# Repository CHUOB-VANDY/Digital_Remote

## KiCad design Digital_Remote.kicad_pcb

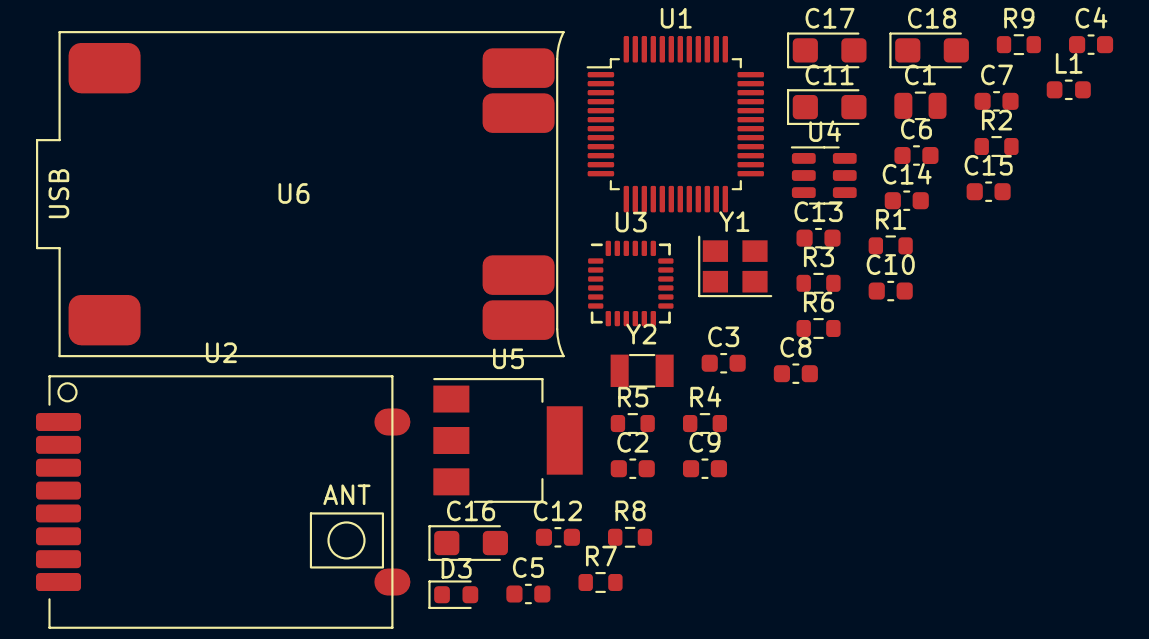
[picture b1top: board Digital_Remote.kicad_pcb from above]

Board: 2 copper layers, 37 parts (0 on the bottom side), 24 nets, no tracks yet.

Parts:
C1: 4.7u; C_0805_2012Metric
C2, C3, C4, C5, C13, C14: 100n; C_0603_1608Metric
C6: 1u; C_0603_1608Metric
C7, C8, C9, C10: 20p; C_0603_1608Metric
C11, C16, C17, C18: 22uF/6V; CP_EIA-3216-10_Kemet-I
C12: 10n; C_0603_1608Metric
C15: 2.2n; C_0603_1608Metric
D3: LED_Small; LED_0603_1608Metric
L1: 4.7nH; L_0603_1608Metric
R1, R2, R6: 10k; R_0603_1608Metric
R3, R4, R5: 4k7; R_0603_1608Metric
R7: 24k; R_0603_1608Metric
R8: 3k3; R_0603_1608Metric
R9: 1k; R_0603_1608Metric
U1: STM32F103C8Tx; LQFP-48_7x7mm_P0.5mm
U2: AS01-SPI
U3: MPU-6050; InvenSense_QFN-24_4x4mm_P0.5mm
U4: MT3608; SOT-23-6
U5: AMS1117-3.3; SOT-223-3_TabPin2
U6: TP4056
Y1: 8Mhz; Crystal_SMD_3225-4Pin_3.2x2.5mm
Y2: 32KHz; Crystal_SMD_3215-2Pin_3.2x1.5mm

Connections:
+3.3VA: C5.1, C6.1, L1.2, U1.9 (VDDA)
+3V3: C1.1, C2.1, C3.1, C4.1, C11.1, C12.2, C13.1, C18.1, L1.1, R1.1, R3.1, R4.1, R9.1, U1.24 (VDD), U1.36 (VDD), U1.48 (VDD), U2.1 (VCC), U3.8 (VDDIO), U3.13 (VDD), U5.2 (VO)
+5V: C17.1, R7.1, U5.3 (VI)
/BOOTO: R2.2, U1.44 (BOOT0)
/Buzzer: R5.1, U1.38 (PA15)
/CPOUT: C15.1, U3.20 (CPOUT)
/HSE_IN: C7.1, U1.5 (PD0), Y1.1
/HSE_OUT: C8.1, U1.6 (PD1), Y1.3
/I2C1_SCL: R3.2, U1.21 (PB10), U3.23 (SCL)
/I2C1_SDA: R4.2, U1.46 (PB9), U3.24 (SDA)
/LSE_IN: C9.1, U1.3 (PC14), Y2.1
/LSE_OUT: C10.1, U1.4 (PC15), Y2.2
/NRF_CE: U1.30 (PA9), U2.3 (CSN)
/NRF_CSN: U1.29 (PA8), U2.2 (CE)
/NRST: R1.2, U1.7 (NRST)
/REGOUT: C14.1, U3.10 (REGOUT)
/SPI2_MISO: U1.27 (PB14), U2.6 (MISO)
/SPI2_MOSI: U1.28 (PB15), U2.5 (MOSI)
/SPI2_SCK: U1.26 (PB13), U2.4 (SCK)
/VIN: C16.1, U4.5 (IN)
GND: C1.2, C2.2, C3.2, C4.2, C5.2, C6.2, C7.2, C8.2, C9.2, C10.2, C11.2, C12.1, C13.2, C14.2, C15.2, C16.2, C17.2, C18.2, D3.1 (K), R2.1, R6.1, R8.2, U1.8 (VSSA), U1.23 (VSS), U1.35 (VSS), U1.47 (VSS), U2.8 (GND), U3.1 (CLKIN), U3.9 (AD0), U3.11 (FSYNC), U3.18 (GND), U4.2 (GND), U5.1 (GND), U6.2 (P-), U6.4 (B-), Y1.2, Y1.4
unnamed: D3.2 (A), R9.2
unnamed: R5.2, R6.2
unnamed: R7.2, R8.1, U4.3 (FB)

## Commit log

2022-09-22 Change schematic
